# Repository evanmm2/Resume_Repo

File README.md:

This Git repository holds the code and data for projects done for classes in college.
Class descriptions:

CS225- Data abstractions: elementary data structures (lists, stacks, queues, and trees) and their implementation using an object-oriented programming language. 
Solutions to a variety of computational problems such as search on graphs and trees. Elementary analysis of algorithms. Class covers a variety of data structures using C and C++,
as well as basic ISAs.

ECE385- This course is designed to give students in computer and electrical engineering an ability to design, build, and debug digital systems that include programmable logic, 
microprocessors, memory systems, and peripherals. Class covers Combinational logic circuits, Storage Elements, Hazards and race conditions, Circuit characteristics (fanout, 
delays, etc.), Field Programmable Gate Arrays (FPGAs), Combinational networks (adders, multiplexes, etc.) in SystemVerilog, Sequential networks (counters, shift registers, etc.) 
in SystemVerilog, Synchronous state machines, Static timing analysis, clock domains, metastability, synchronization, Logic simulation and testbenches, Microprocessors and 
system on chip, Project using a microprocessor and system on chip concepts. For the class, designed a fully function FPGA tetris that worked on a VGA monitor with partner.

ECE425- Complementary Metal-Oxide Semiconductor (CMOS) technology and theory; CMOS circuit and logic design; layout rules and techniques; circuit characterization and 
performance estimation; CMOS subsystem design; Very-Large-Scale Integrated (VLSI) systems design methods; VLSI Computer Aided Design (CAD) tools; workstation-based custom 
VLSI chip design using concepts of cell hierarchy; final project involving specification, design, and evaluation of a VLSI chip or VLSI CAD program; written report and oral p
resentation on the final project. 

ECE391- Introduction to the concepts and abstractions central to the development of modern computing systems, with an emphasis on the systems software that controls interaction 
between devices and other hardware and application programs. Material includes input-output semantics, synchronization, interrupts, multitasking, virtualization of abstractions. 
Emphasis on learning to operate effectively in teams.

ECE411- Basic computer organization and design: integer and floating-point computer arithmetic; control unit design; pipelining; system interconnect; memory organization; 
I/O design; reliability and performance evaluation. Laboratory for computer design implementation, simulation, and layout.

ECE Final Project (Senior Design)- Design and implement a project over the course of a semester with a team. Made a pressure based foot controller. Folder only has EAGLE files for circuit design.

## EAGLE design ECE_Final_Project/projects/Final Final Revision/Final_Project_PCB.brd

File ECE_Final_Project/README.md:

PCB schematic is in the projects/Final_Final_Revision folder

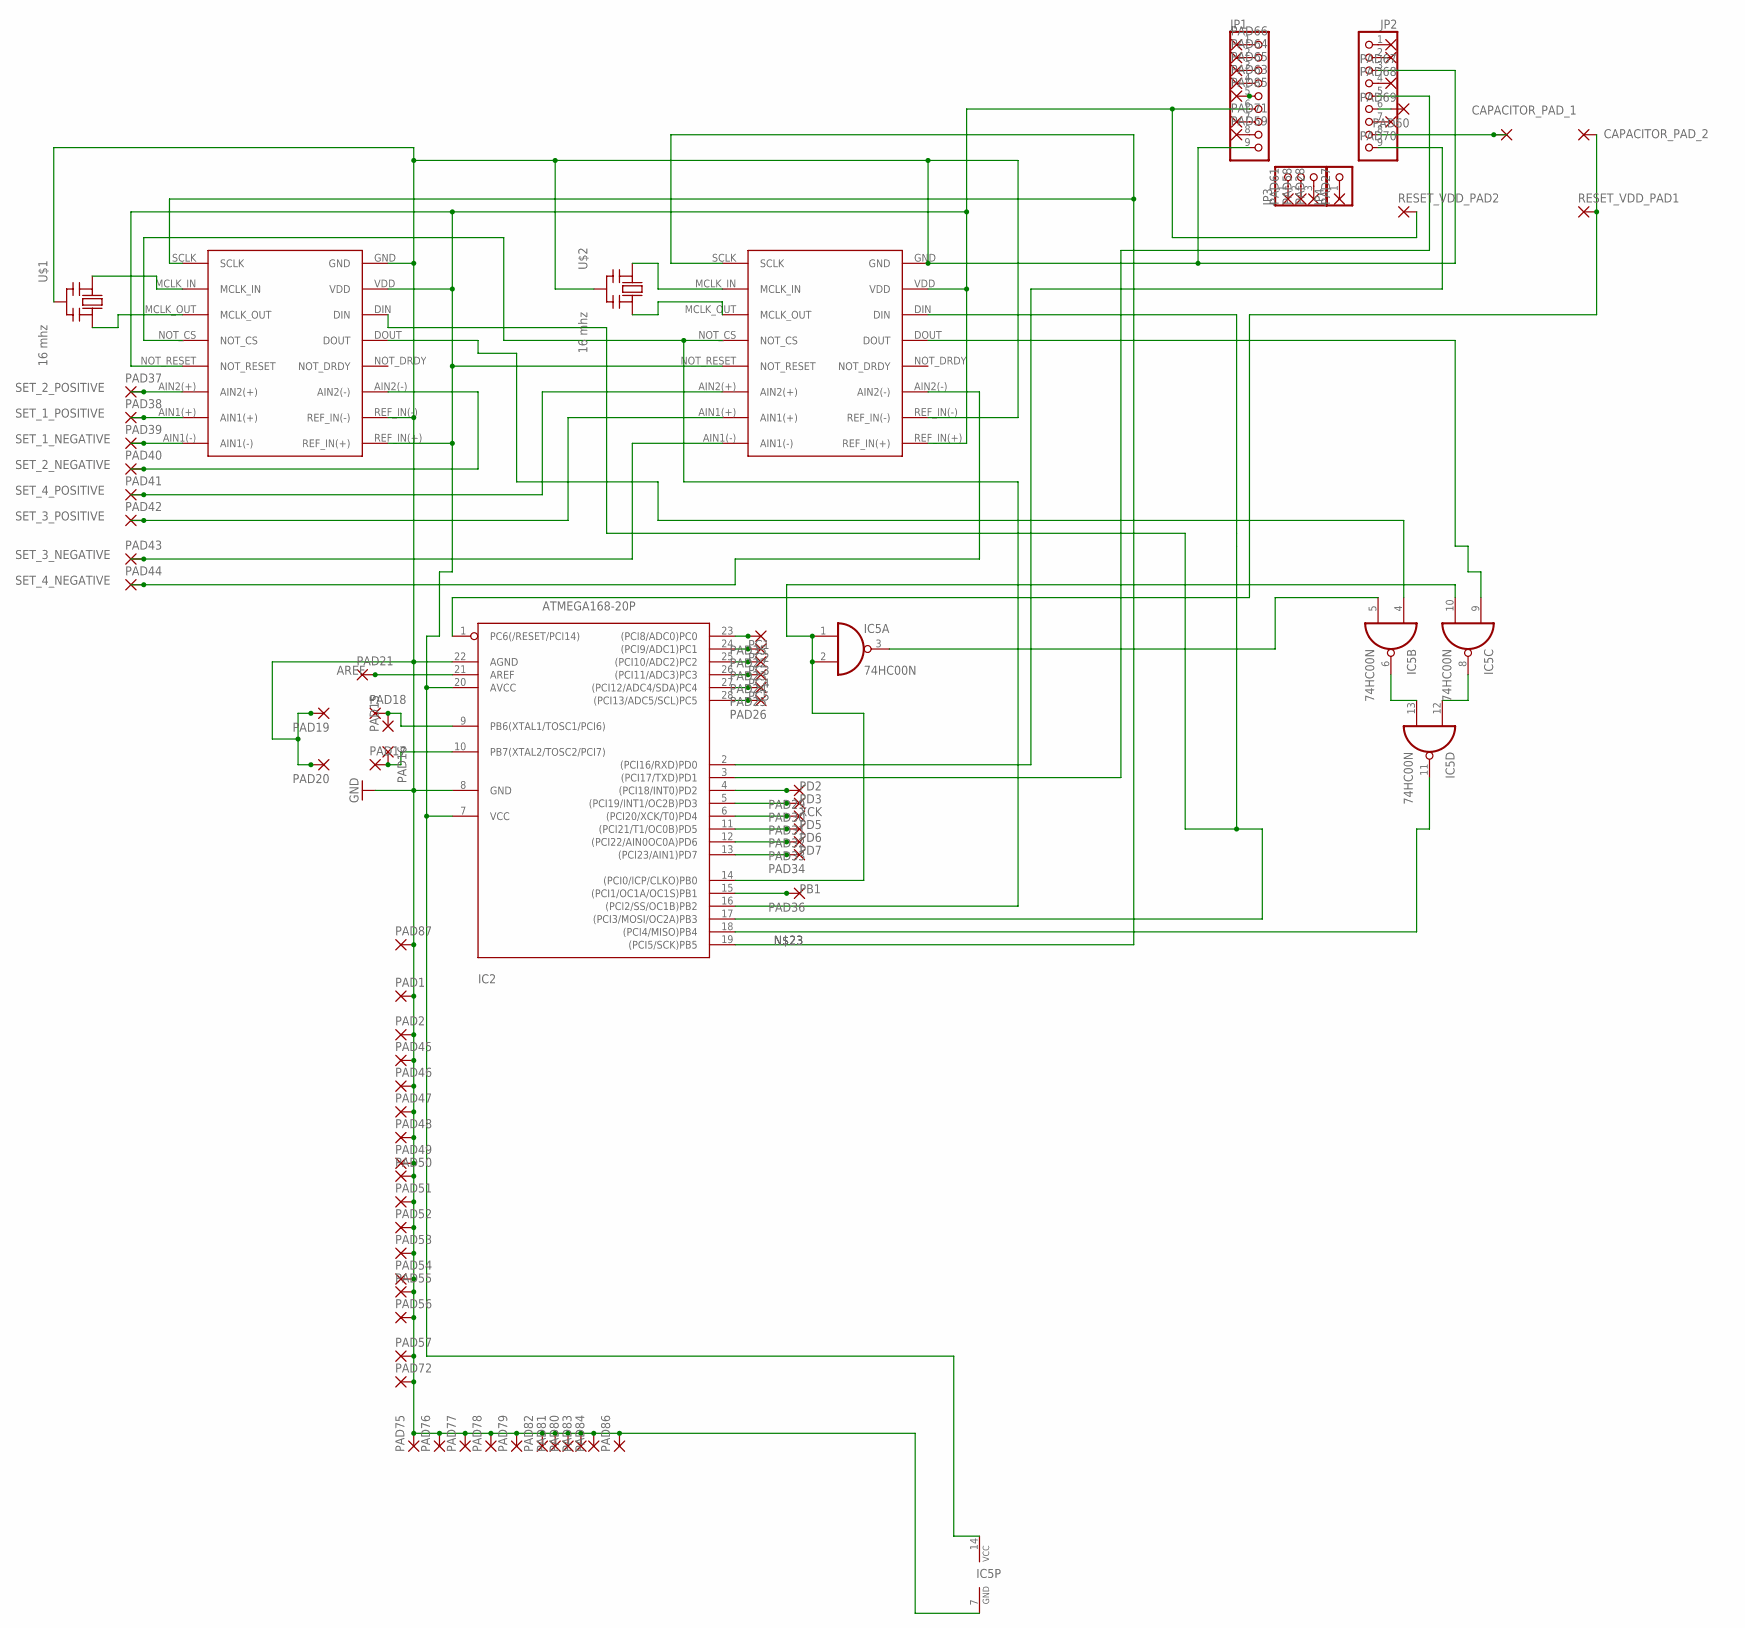
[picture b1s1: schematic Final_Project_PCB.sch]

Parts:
AMPLIFIER1, AMPLIFIER2: AD7705BNZ
CAPACITOR_PAD_1, CAPACITOR_PAD_2: 1,6/0,8
IC2: ATMEGA168-20P; DIL28-3
IC5: 74HC00N; DIL14
JP1, JP2: PINHD-1X9; 1X09-BIG
JP3: PINHD-1X3; 1X03
JP4: PINHD-1X1; 1X01
PAD1, PAD2, PAD15, PAD16, PAD17, PAD18, PAD19, PAD20, PAD21, PAD22, PAD23, PAD24, PAD25, PAD26, PAD27, PAD28, PAD29, PAD30, PAD31, PAD32, PAD33, PAD34, PAD35, PAD36, PAD37, PAD38, PAD39, PAD40, PAD41, PAD42, PAD43, PAD44, PAD45, PAD46, PAD47, PAD48, PAD49, PAD50, PAD51, PAD52, PAD53, PAD54, PAD55, PAD56, PAD57, PAD58, PAD59, PAD60, PAD61, PAD63, PAD64, PAD65, PAD66, PAD67, PAD68, PAD69, PAD70, PAD71, PAD72, PAD75, PAD76, PAD77, PAD78, PAD79, PAD80, PAD81, PAD82, PAD83, PAD84, PAD85, PAD86, PAD87: 1,6/0,8
RESET_VDD_PAD1, RESET_VDD_PAD2: 1,6/0,8
U$1, U$2: 16 mhz; CERM_OSC

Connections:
AREF: IC2.21 (AREF), PAD21.1
GND: AMPLIFIER1.GND, AMPLIFIER1.REF_IN(-), AMPLIFIER2.GND, AMPLIFIER2.REF_IN(-), IC2.8 (GND), IC2.22 (AGND), IC5.7 (GND), JP1.9, JP2.3, PAD1.1, PAD2.1, PAD19.1, PAD20.1, PAD45.1, PAD46.1, PAD47.1, PAD48.1, PAD49.1, PAD50.1, PAD51.1, PAD52.1, PAD53.1, PAD54.1, PAD55.1, PAD56.1, PAD57.1, PAD72.1, PAD75.1, PAD76.1, PAD77.1, PAD78.1, PAD79.1, PAD80.1, PAD81.1, PAD82.1, PAD83.1, PAD84.1, PAD86.1, PAD87.1, U$1.P$2 (GND), U$2.P$2 (GND)
unnamed: AMPLIFIER1.MCLK_IN, U$1.P$1 (IN)
unnamed: JP4.1, PAD27.1
unnamed: AMPLIFIER1.MCLK_OUT, U$1.P$3 (OUT)
unnamed: JP3.3, PAD28.1
unnamed: AMPLIFIER2.MCLK_IN, U$2.P$1 (IN)
unnamed: IC2.18 ((PCI4/MISO)PB4), IC5.11 (O)
unnamed: AMPLIFIER1.NOT_CS, AMPLIFIER2.NOT_CS, IC2.16 ((PCI2/SS/OC1B)PB2)
unnamed: AMPLIFIER1.DIN, AMPLIFIER2.DIN, IC2.17 ((PCI3/MOSI/OC2A)PB3)
unnamed: AMPLIFIER2.DOUT, IC5.9 (I0)
unnamed: AMPLIFIER1.DOUT, IC5.4 (I0)
unnamed: JP2.6, PAD60.1
unnamed: IC5.3 (O), IC5.5 (I1)
unnamed: IC5.6 (O), IC5.13 (I1)
unnamed: IC5.8 (O), IC5.12 (I0)
unnamed: JP3.2, PAD58.1
unnamed: IC2.9 (PB6(XTAL1/TOSC1/PCI6)), PAD15.1, PAD18.1
unnamed: IC2.10 (PB7(XTAL2/TOSC2/PCI7)), PAD16.1, PAD17.1
unnamed: JP1.8, PAD59.1
unnamed: AMPLIFIER2.MCLK_OUT, U$2.P$3 (OUT)
unnamed: JP3.1, PAD61.1
unnamed: JP1.5, PAD85.1
unnamed: AMPLIFIER1.SCLK, AMPLIFIER2.SCLK, IC2.19 ((PCI5/SCK)PB5)
unnamed: JP1.4, PAD63.1
unnamed: JP1.2, PAD64.1
unnamed: JP1.3, PAD65.1
unnamed: JP1.1, PAD66.1
unnamed: JP2.1, PAD67.1
unnamed: JP2.2, PAD68.1
unnamed: JP2.4, PAD69.1
unnamed: JP2.7, PAD70.1
unnamed: CAPACITOR_PAD_1.1, JP2.8
unnamed: CAPACITOR_PAD_2.1, IC2.1 (PC6(/RESET/PCI14)), RESET_VDD_PAD1.1
unnamed: AMPLIFIER1.NOT_RESET, AMPLIFIER1.REF_IN(+), AMPLIFIER1.VDD, AMPLIFIER2.NOT_RESET, AMPLIFIER2.REF_IN(+), AMPLIFIER2.VDD, IC2.7 (VCC), IC2.20 (AVCC), IC5.14 (VCC), JP1.6, RESET_VDD_PAD2.1
unnamed: IC2.23 ((PCI8/ADC0)PC0), PAD35.1
unnamed: JP1.7, PAD71.1
PB0: IC2.14 ((PCI0/ICP/CLKO)PB0), IC5.1 (I0), IC5.2 (I1), IC5.10 (I1)
PB1: IC2.15 ((PCI1/OC1A/OC1S)PB1), PAD36.1
PC1: IC2.24 ((PCI9/ADC1)PC1), PAD22.1
PC2: IC2.25 ((PCI10/ADC2)PC2), PAD23.1
PC3: IC2.26 ((PCI11/ADC3)PC3), PAD24.1
PC4: IC2.27 ((PCI12/ADC4/SDA)PC4), PAD25.1
PC5: IC2.28 ((PCI13/ADC5/SCL)PC5), PAD26.1
PD2: IC2.4 ((PCI18/INT0)PD2), PAD29.1
PD3: IC2.5 ((PCI19/INT1/OC2B)PD3), PAD30.1
PD5: IC2.11 ((PCI21/T1/OC0B)PD5), PAD32.1
PD6: IC2.12 ((PCI22/AIN0OC0A)PD6), PAD33.1
PD7: IC2.13 ((PCI23/AIN1)PD7), PAD34.1
RXD: IC2.2 ((PCI16/RXD)PD0), JP2.9
SET_1_NEGATIVE: AMPLIFIER1.AIN1(-), PAD39.1
SET_1_POSITIVE: AMPLIFIER1.AIN1(+), PAD38.1
SET_2_NEGATIVE: AMPLIFIER1.AIN2(-), PAD40.1
SET_2_POSITIVE: AMPLIFIER1.AIN2(+), PAD37.1
SET_3_NEGATIVE: AMPLIFIER2.AIN1(-), PAD43.1
SET_3_POSITIVE: AMPLIFIER2.AIN1(+), PAD42.1
SET_4_NEGATIVE: AMPLIFIER2.AIN2(-), PAD44.1
SET_4_POSITIVE: AMPLIFIER2.AIN2(+), PAD41.1
TXD: IC2.3 ((PCI17/TXD)PD1), JP2.5
XCK: IC2.6 ((PCI20/XCK/T0)PD4), PAD31.1

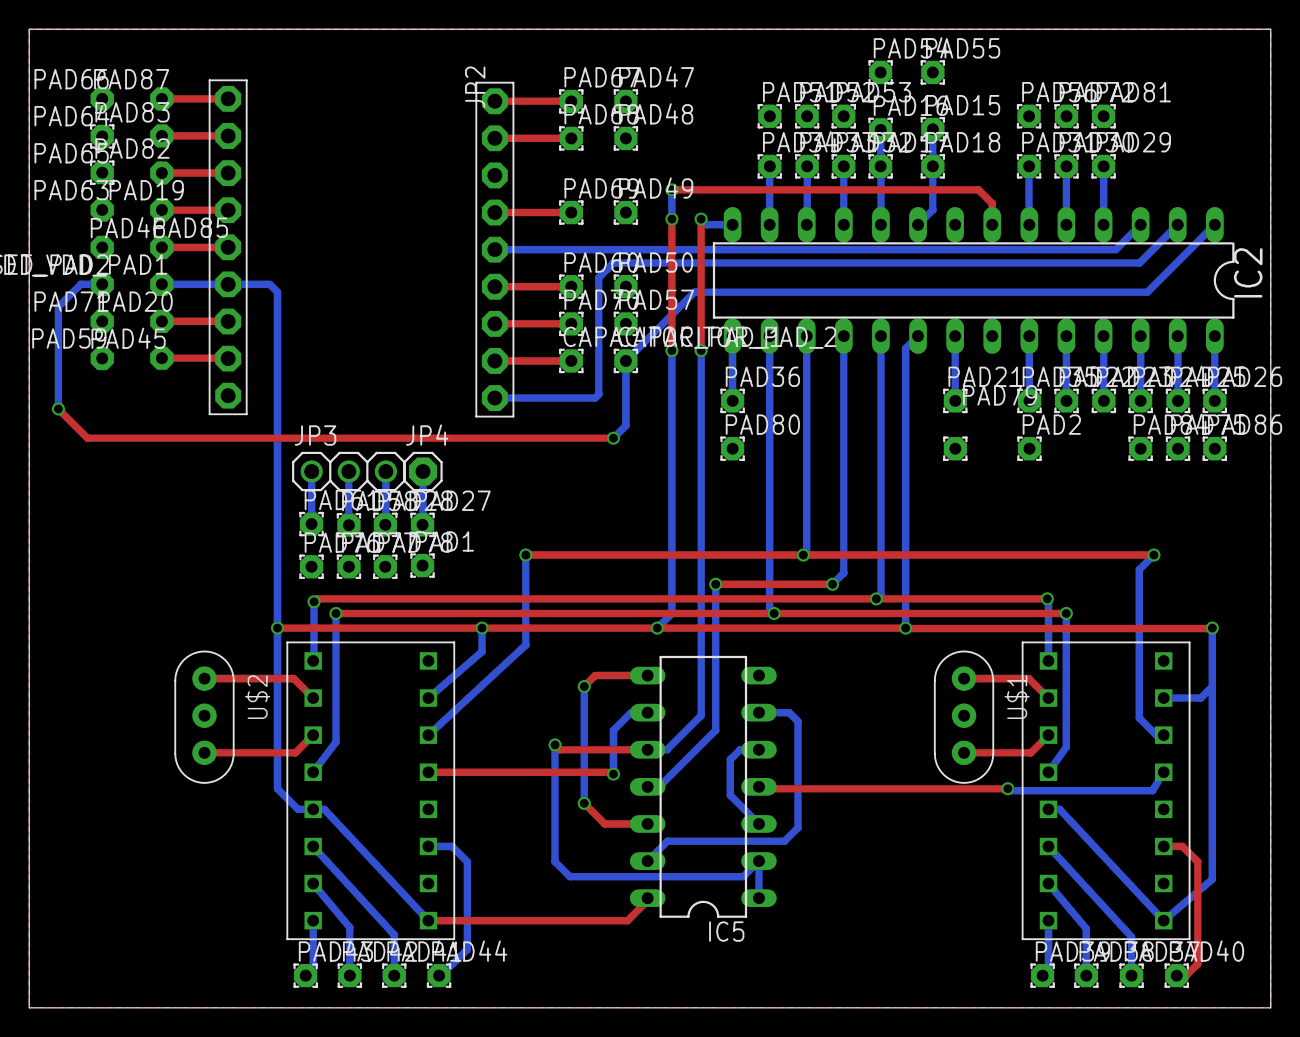
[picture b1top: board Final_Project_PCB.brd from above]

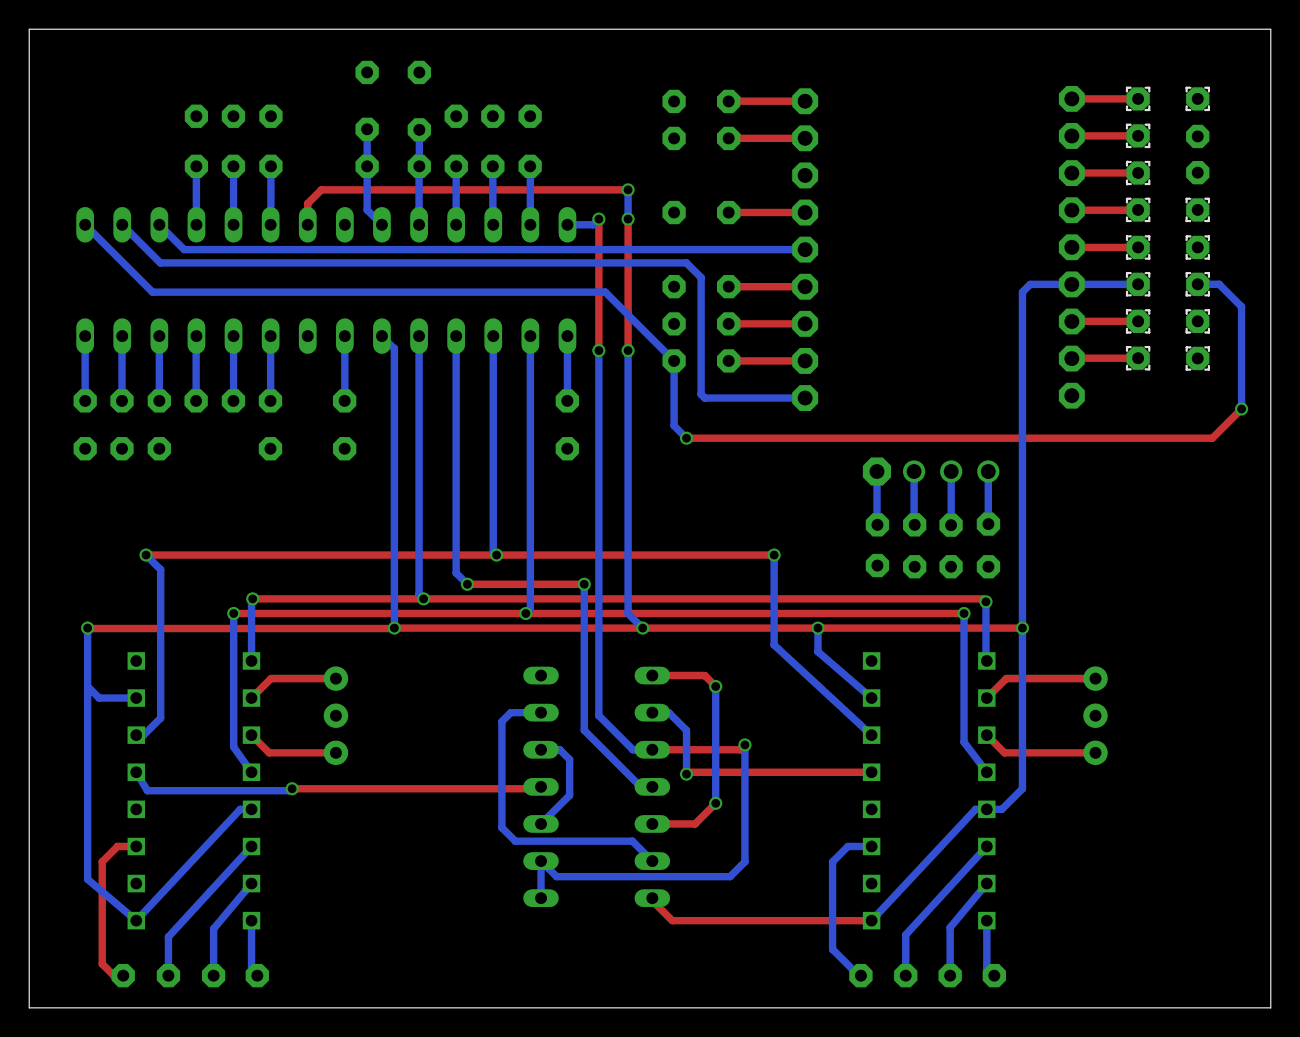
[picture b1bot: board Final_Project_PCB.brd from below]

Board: 2 copper layers, 85.0 x 67.0 mm, 86 parts (14 on the bottom side), 60 nets.

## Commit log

2022-01-22 Create PlaceholderFile
2022-01-24 Adding CS225 Files
2022-02-04 ECE_391 Linux project added to respository
2022-02-05 Linux Code Distrib
2022-02-05 ECE 425 Projects
